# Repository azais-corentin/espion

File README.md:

# espion

Multi-camera IR marker tracking. Each camera board triggers its global-shutter sensor at
the same instant as every other board, finds the IR blobs at 120 fps, computes subpixel
centroids and streams them over Ethernet (UDP). The host triangulates 3D marker positions,
runs calibration and coordinates time sync.

**Status:** firmware and host apps are stubs that build. The camera board's schematic is
captured in KiCad (hierarchical, wired, ERC clean); PCB layout has not started.

## Hardware

A custom KiCad baseboard for a Waveshare ESP32-P4-Core module (ESP32-P4 rev v3, 32 MB
in-package PSRAM, 16 MB flash). The P4 does the vision: it captures an OV9281 (1 MP
monochrome global shutter, MIPI CSI-2, 640×400 binned at 120 fps) triggered on its XVS pin,
and runs blob detection. An 850 nm LED ring (12 × 90° LEDs, ≈ 0.9 A pulses) lights passive
retroreflective markers at room scale (2–5 m). It is gated by the sensor's STROBE output,
with a P4 enable line for dark frames. The P4's own Ethernet MAC with an IP101GRI PHY
(100 Mbit/s) sends UDP to the host and keeps the boards' clocks in sync with PTP (IEEE 1588,
hardware timestamps; target: about 1 µs). The boards elect the PTP grandmaster among
themselves, with automatic failover. The board is powered over PoE (802.3af) or USB-C at
5 V; USB-C also flashes and debugs the P4.

The board's schematic, PCB and 3D view are published at
<https://azais-corentin.github.io/espion/> (Ferrite's web viewer, rebuilt when the board
changes on `main`).

## Layout

| Path | Content |
|---|---|
| `crates/espion-proto/` | no_std UDP wire format shared by firmware and host; the camera stream (raw and JPEG frames, remote settings) is implemented |
| `firmware/cam-p4/` | ESP32-P4: camera, blob detection, XVS trigger, LED gating, Ethernet/UDP, PTP sync |
| `firmware/esp32p4-cache/` | no_std cache maintenance for the P4 behind one lock shared by both cores, and the cache prefetch set-up |
| `firmware/esp32p4-csi/` | no_std MIPI CSI-2 receiver driver for the P4 (esp-hal lacks one) |
| `firmware/esp32p4-jpeg/` | no_std hardware JPEG encoder driver for the P4, greyscale (esp-hal lacks one) |
| `firmware/esp32p4-perf/` | no_std performance counters of the P4: cycles, instructions, branches, mispredictions, stores, cache hits and misses; marker pins through the dedicated-IO CSRs |
| `firmware/esp32p4-pie/` | no_std PIE (128-bit vector) kernels for the P4 on stable Rust: instruction encoders and the dark-skip scan |
| `firmware/espion-core1/` | no_std runner of the blob detector on a bare second core of the P4, and core 0's handle that starts and watches it; optional marker pins for a logic analyser |
| `firmware/espion-vision/` | no_std blob detector: threshold, 8-connected components, intensity-weighted subpixel centroids, on RAW8 and RAW10 rows; tested on the host |
| `firmware/poc-p4-stream/` | Proof of concept on the Waveshare ESP32-P4-ETH: streams the OV9281 to the host over Ethernet (raw or JPEG) and takes its settings from there |
| `firmware/ov9281/` | no_std OV9281 sensor driver: computes a mode (format, size, crop/binning, frame rate) and drives the sensor over SCCB |
| `host/espion-server/` | UDP receive + triangulation (CLI) |
| `host/espion-viewer/` | egui live view |
| `host/espion-calib/` | Intrinsics + extrinsics calibration |
| `host/espion-sync/` | Time-sync coordinator |
| `host/poc-viewer/` | Live view and control of the `poc-p4-stream` camera, with a fake camera for working without the board |
| `hardware/` | KiCad project (`espion-cam/`) and local libraries with their 3D models (`lib/`) |
| `docs/` | [architecture](docs/architecture.md), [protocol](docs/protocol.md), [timing](docs/timing.md), [board design](docs/hardware/README.md) |

## Dev environment

Needs Nix with flakes. The dev shell provides Rust 1.99.1 with the host and
`riscv32imafc-unknown-none-elf` (P4) targets, espflash, probe-rs, KiCad 10 and SolidCraft
(builds the library parts' 3D models).

```sh
direnv allow        # or: nix develop
```

Local overrides (e.g. `ESPFLASH_PORT`) go in `.envrc.local`, which is git-ignored.

Entering the dev shell installs the git hooks (`hk.pkl`): commit messages must follow
[Conventional Commits](https://www.conventionalcommits.org/), with the scopes in
`cog.toml`. See the Commits section of `AGENTS.md`.

## Build, flash, run

Host workspace (repo root; includes `espion-proto`):

```sh
cargo build --workspace
cargo test --workspace
cargo run -p espion-server   # TODO: stub, does nothing yet
cargo run -p espion-viewer   # TODO: stub
cargo run -p espion-calib    # TODO: stub
cargo run -p espion-sync     # TODO: stub
cargo run -p poc-viewer --release             # the ESP32-P4-ETH camera on eth0
cargo run -p poc-viewer --release -- --fake   # the same against a fake camera, no board
```

Firmware (own target, runner and lockfile; run from its directory):

```sh
cd firmware/cam-p4 && cargo build --release   # also builds firmware/esp32p4-csi

# TODO: untested (no board yet). The P4's USB Serial/JTAG shows up on the board's USB-C
# port. Flashes and opens the monitor:
cd firmware/cam-p4 && ESPFLASH_PORT=/dev/ttyACM0 cargo run --release
```

Hardware:

```sh
kicad hardware/espion-cam/espion-cam.kicad_pro
kicad-cli sch erc hardware/espion-cam/espion-cam.kicad_sch

# Rebuild a library part's 3D model from its SolidCraft script:
solidcraft-cli run hardware/lib/3d-src/<Footprint>.json --out hardware/lib/<Library>.3dshapes/<Footprint>.step
```

Library conventions and KLC checks: [hardware/lib/README.md](hardware/lib/README.md).

## License

Code: [MIT](LICENSE-MIT) or [Apache-2.0](LICENSE-APACHE), at your option.
Hardware (`hardware/`): [CERN-OHL-P-2.0](hardware/LICENSE).

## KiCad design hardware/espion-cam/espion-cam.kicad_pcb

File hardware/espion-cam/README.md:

# espion-cam

KiCad project for the espion camera board: a baseboard for the Waveshare ESP32-P4-Core
module. The schematic is captured and ERC clean: a root sheet and seven hierarchical sheets
(power, mcu, ethernet, camera, led_driver, led_ring, imu), with the multi-signal interfaces
crossing sheets as buses. The board is fully placed and routed (4 layers, 64 × 64 mm,
JLCPCB Economic PCBA on the top side, hand-soldered parts listed in `.omp/kicad.json`).
Licensed under CERN-OHL-P-2.0 (`../LICENSE`).

## Board

- **MCU:** U6 Waveshare ESP32-P4-Core module (bottom side, hand-soldered, not on the stencil).
  Symbol `MCU_Module_Waveshare:ESP32-P4-Core`, footprint
  `Module_Waveshare:Waveshare_ESP32-P4-Core_HandSolder` (`../lib/`).
  [mcu](../../docs/hardware/mcu.md#module)
- **Camera:** off-board OV9281 global-shutter mono module behind a lens cutout, on a 15-pin 1.0 mm
  FFC (MIPI CSI-2, 2 lanes) through a notch in the board edge into J4 (AFA07 family, bottom
  contact). XVS (GPIO7) and STROBE come from the module's pads over a JST-SH 4-pin pigtail into J3:
  XVS through the R40/R44 divider, an assembly option; STROBE through U7 Tech Public TP74LV1T34 to the LED
  gate and GPIO12 (ETM capture). The CSI lanes run straight from J4 to U6, with no series-resistor positions.
  [camera](../../docs/hardware/camera.md)
- **LED:** 850 nm ring D4–D15, 12 × A-SC880IR3C in one string around the lens cutout. U10
  TPS61170 boost straight from +5V (`BST_EN`, GPIO53; PWM sets the
  output) into the storage capacitors C46/C47, U11 TLV9061 + Q1 HL2310A (SOT-23) current sink (R69
  sense) gated by `STROBE ∧ LED_EN` in U9 SN74LVC1G97 (`LED_EN`, GPIO11), with a hardware
  timeout per pulse behind the firmware exposure cap. No continuous-on mode. Firmware keeps
  +32V just above the string from a divider on Q1's drain (R70/R76, `LED_K_SENSE`, GPIO23), a
  required headroom loop: Q1 is not rated for full boost output.
  [led](../../docs/hardware/led.md)
- **Ethernet:** U1 IP101G PHY on RMII (Y1 crystal; the PHY supplies the REF_CLK), J1 LINK-PP
  LPJG0926HENL MagJack (bottom side, hand-soldered) with all four line-side centre taps brought out,
  its LEDs driven by the PHY, PPS and PHY reset test points. `PHY_RST_N` GPIO22.
  [ethernet](../../docs/hardware/ethernet.md)
- **Power:** U2 DP1435-5V IEEE 802.3af PoE PD module (isolated, bottom side, hand-soldered)
  straight to U4 TPS2121 priority mux (internal reference), OR-ed with USB-C 5 V (source
  on `PWR_SRC`, GPIO2); U3 TLV62569 buck to 3.3 V. [power](../../docs/hardware/power.md)
- **USB-C:** J2 straight to the P4's USB Serial/JTAG (no hub, GPIO24/25), U5 SRV05-4 ESD
  protection, D2 H7VHD3UA VBUS TVS. VBUS is not sensed: the D+ pull-up stays on.
  [mcu](../../docs/hardware/mcu.md#usb-c)
- **Status and buttons:** D1 YY-0807BRGK26 RGB status LED (`STATUS_LED`, GPIO13); SW1
  RESET and SW2 BOOT.
  [mcu](../../docs/hardware/mcu.md#status-led)
- **IMU:** U12 MSA3S02 3-axis accelerometer on its own I²C bus (GPIO3/4), INT1 on GPIO51: the
  motion interrupt flags a bumped camera, the accelerometer gives the gravity vector for rig
  calibration (no gyroscope). [imu](../../docs/hardware/imu.md)
- **Mechanical:** 4 × M3 plated mounting holes H1–H4, each pad on GND, kept clear of the PoE
  cable-side copper; 3 NPTH tooling holes TOOL1–TOOL3 (board-only) for JLCPCB Economic PCBA.
  [layout](../../docs/hardware/layout.md#board-and-stack-up)

Assembly: everything on the top side is machine-placed by JLCPCB Economic PCBA except the
hand-assembly list (`assembly.hand` in `.omp/kicad.json`; reasons in
[layout](../../docs/hardware/layout.md#assembly)).

Board design (decisions, requirements and their reasons, formulas, layout constraints,
firmware rules, the checks for the first boards): [`docs/hardware/`](../../docs/hardware/README.md).

The parts list is the schematic: every sourced symbol carries Manufacturer, MPN and LCSC fields,
and the project's BOM preset `Order` exports them. Read it with `kicad_query bom`, or generate
the CSV for each order (from this directory) and don't commit it:

```sh
kicad-cli sch export bom --preset Order -o espion-cam-bom.csv espion-cam.kicad_sch
```

The CSV has the columns Reference, Qty, Value, Footprint, Manufacturer, MPN, LCSC and DNP,
one row per group of identical parts, without DNP parts or parts excluded from the BOM.

Net classes (track widths, clearances, diff-pair geometry) are set in `espion-cam.kicad_pro`
for the JLCPCB JLC04161H-7628 stack-up (4 layers, 1.6 mm). The spacing rules that net
classes can't express (PoE isolation, MIPI CSI spacing and skew, MDI spacing, pair-to-pair spacing and skew, LED_PWR pad
spacing, the U12 LGA lands, hole spacing, power neck-downs and silkscreen) are in the custom
rules file `espion-cam.kicad_dru`; [layout](../../docs/hardware/layout.md#custom-rules) gives each one's reason.

System view: `../../docs/architecture.md`. Timing requirements for XVS, STROBE and PPS:
`../../docs/timing.md`.

## Conventions

- Edit only with KiCad (the dev shell provides KiCad 10). Never hand-edit `.kicad_*` files.
  Agents work through the KiCad toolkit instead (`kicad_query`, `kicad_edit`,
  `kicad_check`, `kicad_render`, `kicad_export`; see `../../AGENTS.md`).
- The schematic and the board are the source of every value. `docs/hardware/` holds
  requirements, decisions, formulas, accepted risks, layout constraints, firmware rules and
  first-board checks, never values the KiCad files hold or that are calculated from them. A
  change updates `../../docs/hardware/` in the same commit when it changes one of those. A
  part change also updates the symbol's Manufacturer, MPN and LCSC fields. A new or removed
  block or IC family updates the board list above. There is no committed BOM file.
- Keep ERC at 0 violations: `kicad-cli sch erc espion-cam.kicad_sch` (from this directory).
- Project-specific symbols, footprints and 3D models go in `../lib/` (conventions and KLC
  checks in `../lib/README.md`), not in global libraries.
- Fabrication outputs (Gerbers, drill files, BOM/CPL exports) and KiCad's `.history/` are
  not committed. Generate the outputs for each release (`kicad_export` writes them to
  `fab/`).

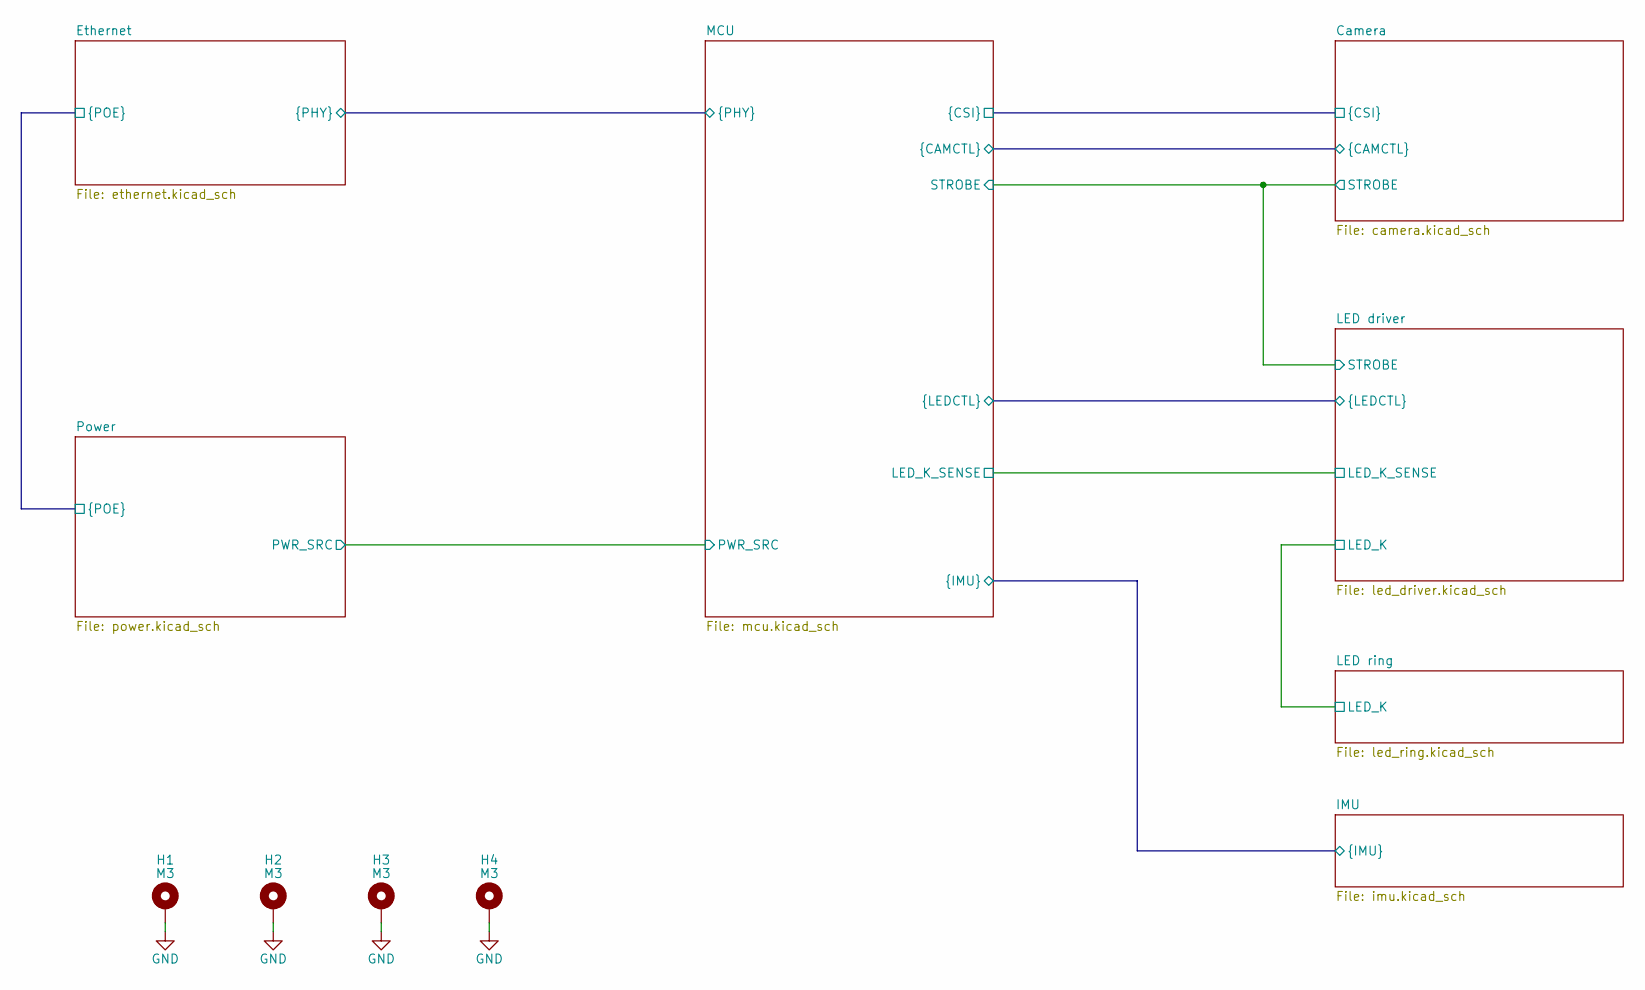
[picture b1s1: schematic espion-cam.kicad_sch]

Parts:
H1, H2, H3, H4: M3; MountingHole_3.2mm_M3_Pad

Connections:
GND: H1.1 (1_1), H2.1 (1_1), H3.1 (1_1), H4.1 (1_1); also elsewhere on the board

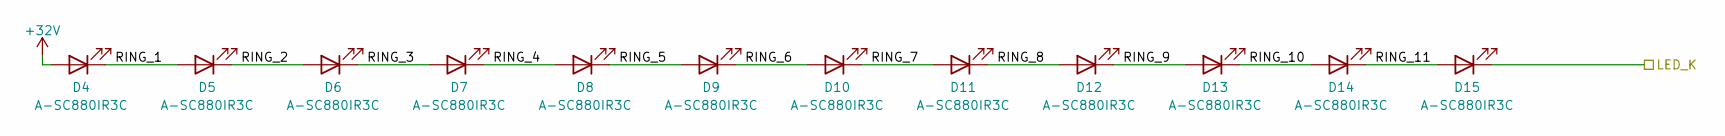
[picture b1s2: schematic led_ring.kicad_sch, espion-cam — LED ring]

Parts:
D4, D5, D6, D7, D8, D9, D10, D11, D12, D13, D14, D15: A-SC880IR3C; LED_Amicc_A-SC880IR3C_3.85x3.85mm; MPN A-SC880IR3C-P03-1T; LCSC C5355470

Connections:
+32V: D4.2 (A); also elsewhere on the board
/LED driver/LED_K: D15.1 (K); also elsewhere on the board
/LED ring/RING_1: D4.1 (K), D5.2 (A)
/LED ring/RING_2: D5.1 (K), D6.2 (A)
/LED ring/RING_3: D6.1 (K), D7.2 (A)
/LED ring/RING_4: D7.1 (K), D8.2 (A)
/LED ring/RING_5: D8.1 (K), D9.2 (A)
/LED ring/RING_6: D9.1 (K), D10.2 (A)
/LED ring/RING_7: D10.1 (K), D11.2 (A)
/LED ring/RING_8: D11.1 (K), D12.2 (A)
/LED ring/RING_9: D12.1 (K), D13.2 (A)
/LED ring/RING_10: D13.1 (K), D14.2 (A)
/LED ring/RING_11: D14.1 (K), D15.2 (A)

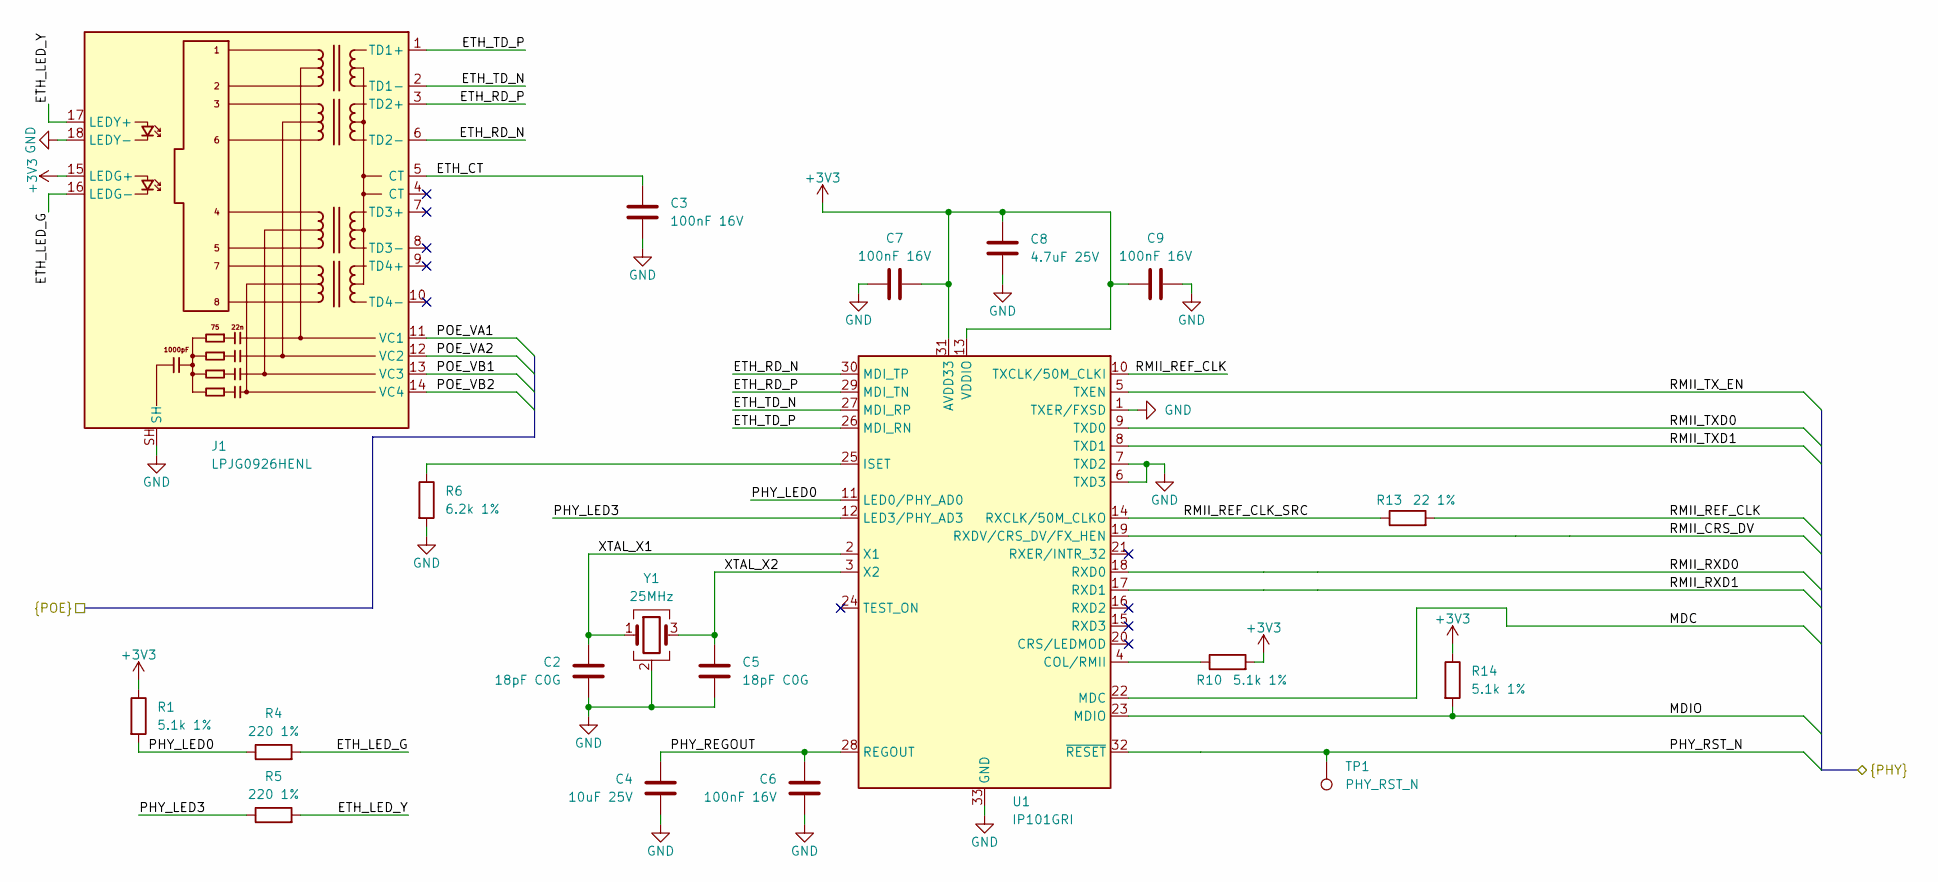
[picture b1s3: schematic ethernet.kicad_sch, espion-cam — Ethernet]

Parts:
C2, C5: 18pF C0G; C_0402_1005Metric; MPN 0402CG180J500NT; LCSC C1549
C3, C6, C7, C9: 100nF 16V; C_0402_1005Metric; MPN CL05B104KO5NNNC; LCSC C1525
C4: 10uF 25V; C_0805_2012Metric; MPN CL21A106KAYNNNE; LCSC C15850
C8: 4.7uF 25V; C_0805_2012Metric; MPN CL21A475KAQNNNE; LCSC C1779
J1: LPJG0926HENL; RJ45_LinkPP_LPJG0926HENL_Horizontal; MPN LPJG0926HENL; LCSC C22457393
R1, R10, R14: 5.1k 1%; R_0402_1005Metric; MPN 0402WGF5101TCE; LCSC C25905
R4, R5: 220 1%; R_0402_1005Metric; MPN 0402WGF2200TCE; LCSC C25091
R6: 6.2k 1%; R_0603_1608Metric; MPN 0603WAF6201T5E; LCSC C4260
R13: 22 1%; R_0402_1005Metric; MPN 0402WGF220JTCE; LCSC C25092
TP1: PHY_RST_N; TestPoint_Pad_D1.0mm
U1: IP101GRI; QFN-32-1EP_4x4mm_P0.4mm_EP2.65x2.65mm; MPN IP101GRI; LCSC C703537
Y1: 25MHz; Crystal_SMD_3225-4Pin_3.2x2.5mm; MPN X1E0000210139; LCSC C91750

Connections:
+3V3: C7.1, C8.1, C9.1, J1.15 (LEDG+), R1.1, R10.2, R14.1, U1.13 (VDDIO), U1.31 (AVDD33); also elsewhere on the board
/Ethernet/ETH_CT: C3.1, J1.5 (CT)
/Ethernet/ETH_LED_G: J1.16 (LEDG-), R4.2
/Ethernet/ETH_LED_Y: J1.17 (LEDY+), R5.2
/Ethernet/ETH_RD_N: J1.6 (TD2-), U1.30 (MDI_TP)
/Ethernet/ETH_RD_P: J1.3 (TD2+), U1.29 (MDI_TN)
/Ethernet/ETH_TD_N: J1.2 (TD1-), U1.27 (MDI_RP)
/Ethernet/ETH_TD_P: J1.1 (TD1+), U1.26 (MDI_RN)
/Ethernet/MDC: U1.22 (MDC); also elsewhere on the board
/Ethernet/MDIO: R14.2, U1.23 (MDIO); also elsewhere on the board
/Ethernet/PHY_LED0: R1.2, R4.1, U1.11 (LED0/PHY_AD0)
/Ethernet/PHY_LED3: R5.1, U1.12 (LED3/PHY_AD3)
/Ethernet/PHY_REGOUT: C4.1, C6.1, U1.28 (REGOUT)
/Ethernet/PHY_RST_N: TP1.1 (1_1), U1.32 (~RESET); also elsewhere on the board
/Ethernet/POE_VA1: J1.11 (VC1); also elsewhere on the board
/Ethernet/POE_VA2: J1.12 (VC2); also elsewhere on the board
/Ethernet/POE_VB1: J1.13 (VC3); also elsewhere on the board
/Ethernet/POE_VB2: J1.14 (VC4); also elsewhere on the board
/Ethernet/RMII_CRS_DV: U1.19 (RXDV/CRS_DV/FX_HEN); also elsewhere on the board
/Ethernet/RMII_REF_CLK: R13.2, U1.10 (TXCLK/50M_CLKI); also elsewhere on the board
/Ethernet/RMII_REF_CLK_SRC: R13.1, U1.14 (RXCLK/50M_CLKO)
/Ethernet/RMII_RXD0: U1.18 (RXD0); also elsewhere on the board
/Ethernet/RMII_RXD1: U1.17 (RXD1); also elsewhere on the board
/Ethernet/RMII_TXD0: U1.9 (TXD0); also elsewhere on the board
/Ethernet/RMII_TXD1: U1.8 (TXD1); also elsewhere on the board
/Ethernet/RMII_TX_EN: U1.5 (TXEN); also elsewhere on the board
/Ethernet/XTAL_X1: C2.1, U1.2 (X1), Y1.1
/Ethernet/XTAL_X2: C5.1, U1.3 (X2), Y1.3
GND: C2.2, C3.2, C4.2, C5.2, C6.2, C7.2, C8.2, C9.2, J1.18 (LEDY-), J1.SH, R6.2, U1.1 (TXER/FXSD), U1.6 (TXD3), U1.7 (TXD2), U1.33 (GND), Y1.2 (G), Y1.4 (G); also elsewhere on the board
unnamed: R10.1, U1.4 (COL/RMII)
unnamed: R6.1, U1.25 (ISET)

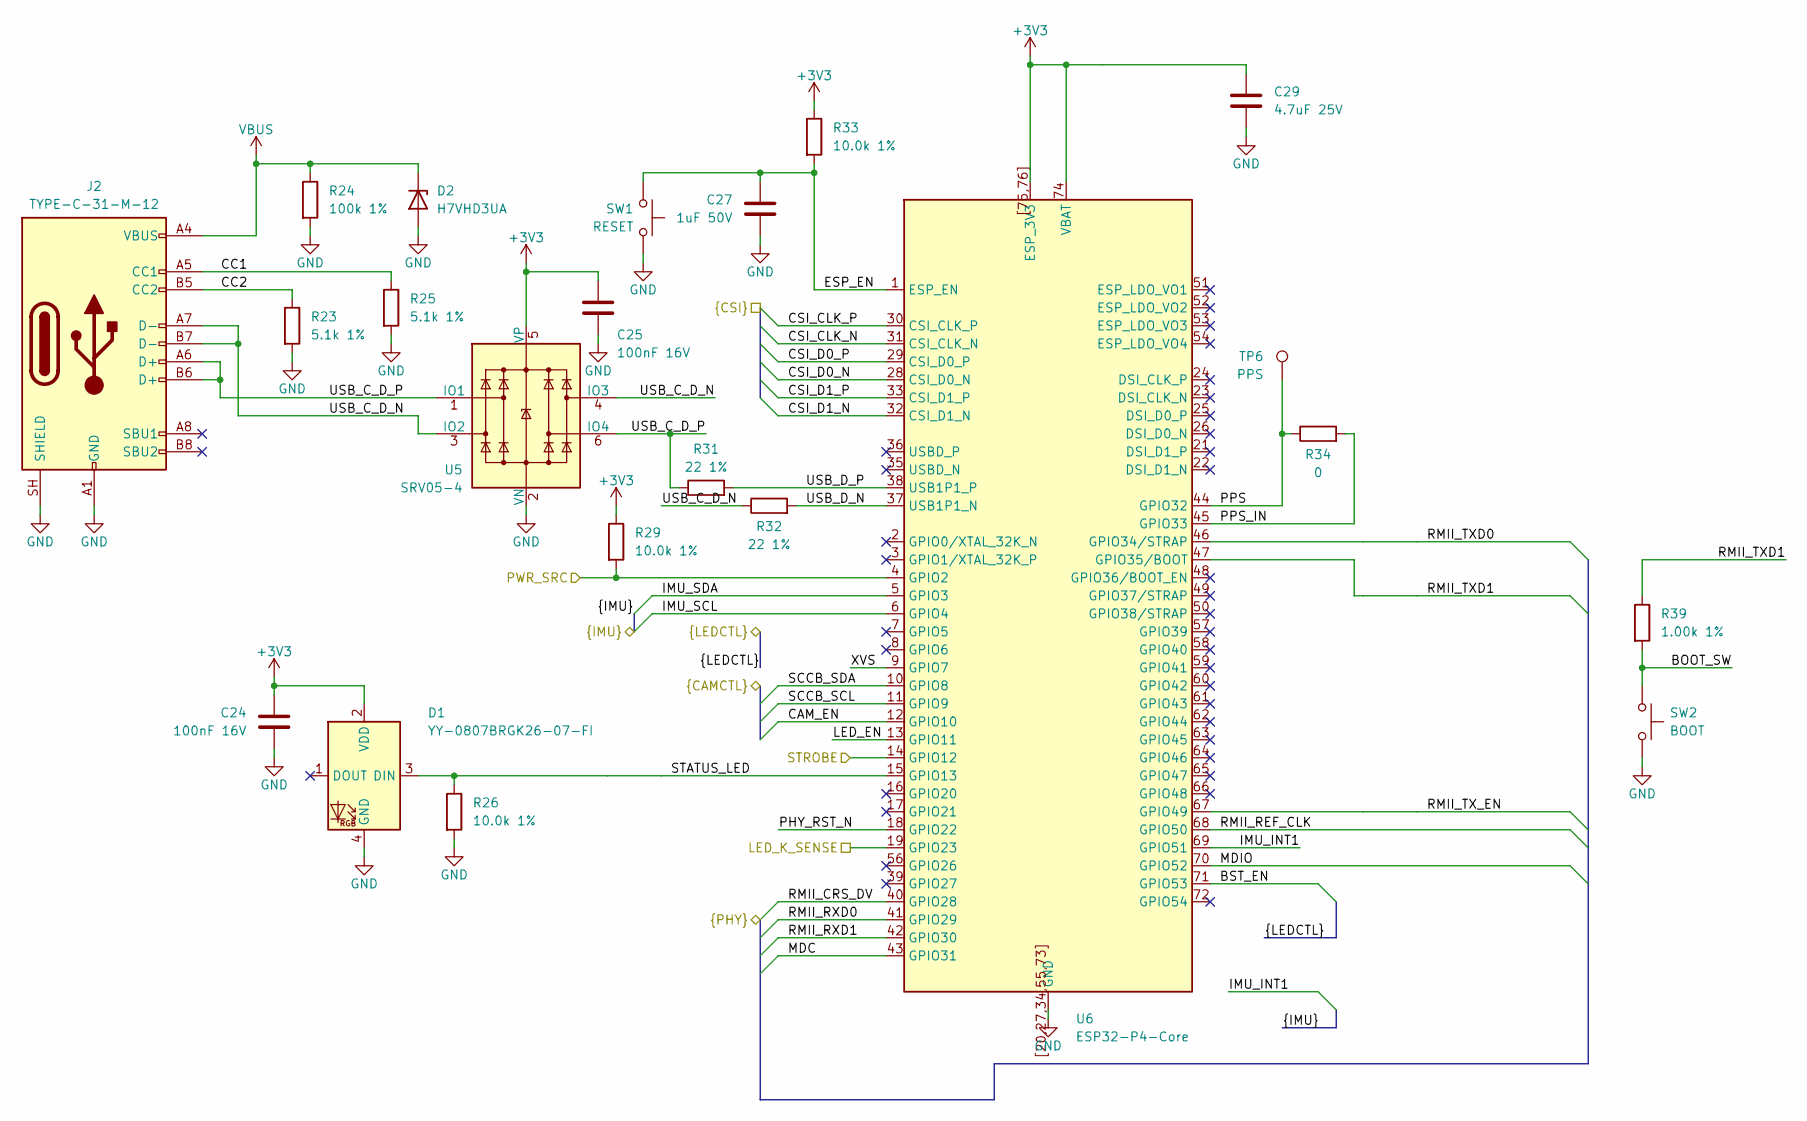
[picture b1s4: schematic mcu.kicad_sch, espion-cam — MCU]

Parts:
C24, C25: 100nF 16V; C_0402_1005Metric; MPN CL05B104KO5NNNC; LCSC C1525
C27: 1uF 50V; C_0805_2012Metric; MPN CL21B105KBFNNNE; LCSC C28323
C29: 4.7uF 25V; C_0805_2012Metric; MPN CL21A475KAQNNNE; LCSC C1779
D1: YY-0807BRGK26-07-FI; LED_Yongyu_YY-0807_2.0x1.7mm; MPN YY-0807BRGK26-07-FI; LCSC C54796802
D2: H7VHD3UA; D_SOD-323_HandSoldering; MPN H7VHD3UA; LCSC C20615807
J2: TYPE-C-31-M-12; USB_C_Receptacle_HRO_TYPE-C-31-M-12; MPN TYPE-C-31-M-12; LCSC C165948
R23, R25: 5.1k 1%; R_0402_1005Metric; MPN 0402WGF5101TCE; LCSC C25905
R24: 100k 1%; R_0402_1005Metric; MPN 0402WGF1003TCE; LCSC C25741
R26, R29, R33: 10.0k 1%; R_0402_1005Metric; MPN 0402WGF1002TCE; LCSC C25744
R31, R32: 22 1%; R_0402_1005Metric; MPN 0402WGF220JTCE; LCSC C25092
R34: 0; R_0402_1005Metric; MPN 0402WGF0000TCE; LCSC C17168
R39: 1.00k 1%; R_0402_1005Metric; MPN 0402WGF1001TCE; LCSC C11702
SW1: RESET; SW_Push_1P1T_XKB_TS-1187A; MPN TS-1187A-B-A-B; LCSC C318884
SW2: BOOT; SW_Push_1P1T_XKB_TS-1187A; MPN TS-1187A-B-A-B; LCSC C318884
TP6: PPS; TestPoint_Pad_D1.0mm
U5: SRV05-4; SOT-23-6; MPN SRV05-4; LCSC C7420376
U6: ESP32-P4-Core; Waveshare_ESP32-P4-Core_HandSolder; MPN ESP32-P4-Core (SKU 36096)

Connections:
+3V3: C24.1, C25.1, C29.1, D1.2 (VDD), R29.1, R33.1, U5.5 (VP), U6.74 (VBAT), U6.75 (ESP_3V3), U6.76 (ESP_3V3), U6.[75,76] (ESP_3V3); also elsewhere on the board
/Camera/CAM_EN: U6.12 (GPIO10); also elsewhere on the board
/Camera/CSI_CLK_N: U6.31 (CSI_CLK_N); also elsewhere on the board
/Camera/CSI_CLK_P: U6.30 (CSI_CLK_P); also elsewhere on the board
/Camera/CSI_D0_N: U6.28 (CSI_D0_N); also elsewhere on the board
/Camera/CSI_D0_P: U6.29 (CSI_D0_P); also elsewhere on the board
/Camera/CSI_D1_N: U6.32 (CSI_D1_N); also elsewhere on the board
/Camera/CSI_D1_P: U6.33 (CSI_D1_P); also elsewhere on the board
/Camera/SCCB_SCL: U6.11 (GPIO9); also elsewhere on the board
/Camera/SCCB_SDA: U6.10 (GPIO8); also elsewhere on the board
/Camera/STROBE: U6.14 (GPIO12); also elsewhere on the board
/Camera/XVS: U6.9 (GPIO7); also elsewhere on the board
/Ethernet/MDC: U6.43 (GPIO31); also elsewhere on the board
/Ethernet/MDIO: U6.70 (GPIO52); also elsewhere on the board
/Ethernet/PHY_RST_N: U6.18 (GPIO22); also elsewhere on the board
/Ethernet/RMII_CRS_DV: U6.40 (GPIO28); also elsewhere on the board
/Ethernet/RMII_REF_CLK: U6.68 (GPIO50); also elsewhere on the board
/Ethernet/RMII_RXD0: U6.41 (GPIO29); also elsewhere on the board
/Ethernet/RMII_RXD1: U6.42 (GPIO30); also elsewhere on the board
/Ethernet/RMII_TXD0: U6.46 (GPIO34/STRAP); also elsewhere on the board
/Ethernet/RMII_TXD1: R39.1, U6.47 (GPIO35/BOOT); also elsewhere on the board
/Ethernet/RMII_TX_EN: U6.67 (GPIO49); also elsewhere on the board
/LED driver/LED_K_SENSE: U6.19 (GPIO23); also elsewhere on the board
/MCU/BOOT_SW: R39.2, SW2.1
/MCU/BST_EN: U6.71 (GPIO53); also elsewhere on the board
/MCU/CC1: J2.A5 (CC1), R25.1
/MCU/CC2: J2.B5 (CC2), R23.1
/MCU/ESP_EN: C27.1, R33.2, SW1.1, U6.1 (ESP_EN)
/MCU/IMU_INT1: U6.69 (GPIO51); also elsewhere on the board
/MCU/IMU_SCL: U6.6 (GPIO4); also elsewhere on the board
/MCU/IMU_SDA: U6.5 (GPIO3); also elsewhere on the board
/MCU/LED_EN: U6.13 (GPIO11); also elsewhere on the board
/MCU/PPS: R34.1, TP6.1 (1_1), U6.44 (GPIO32)
/MCU/PPS_IN: R34.2, U6.45 (GPIO33)
/MCU/PWR_SRC: R29.2, U6.4 (GPIO2); also elsewhere on the board
/MCU/STATUS_LED: D1.3 (DIN), R26.1, U6.15 (GPIO13)
/MCU/USB_C_D_N: J2.A7 (D-), J2.B7 (D-), R32.1, U5.3 (IO2), U5.4 (IO3)
/MCU/USB_C_D_P: J2.A6 (D+), J2.B6 (D+), R31.1, U5.1 (IO1), U5.6 (IO4)
/MCU/USB_D_N: R32.2, U6.37 (USB1P1_N)
/MCU/USB_D_P: R31.2, U6.38 (USB1P1_P)
GND: C24.2, C25.2, C27.2, C29.2, D1.4 (GND), D2.2 (A), J2.A1 (GND), J2.A12 (GND), J2.B1 (GND), J2.B12 (GND), J2.SH (SHIELD), R23.2, R24.2, R25.2, R26.2, SW1.2, SW2.2, U5.2 (VN), U6.20 (GND), U6.27 (GND), U6.34 (GND), U6.55 (GND), U6.73 (GND), U6.[20,27,34,55,73] (GND); also elsewhere on the board
VBUS: D2.1 (K), J2.A4 (VBUS), J2.A9 (VBUS), J2.B4 (VBUS), J2.B9 (VBUS), R24.1; also elsewhere on the board

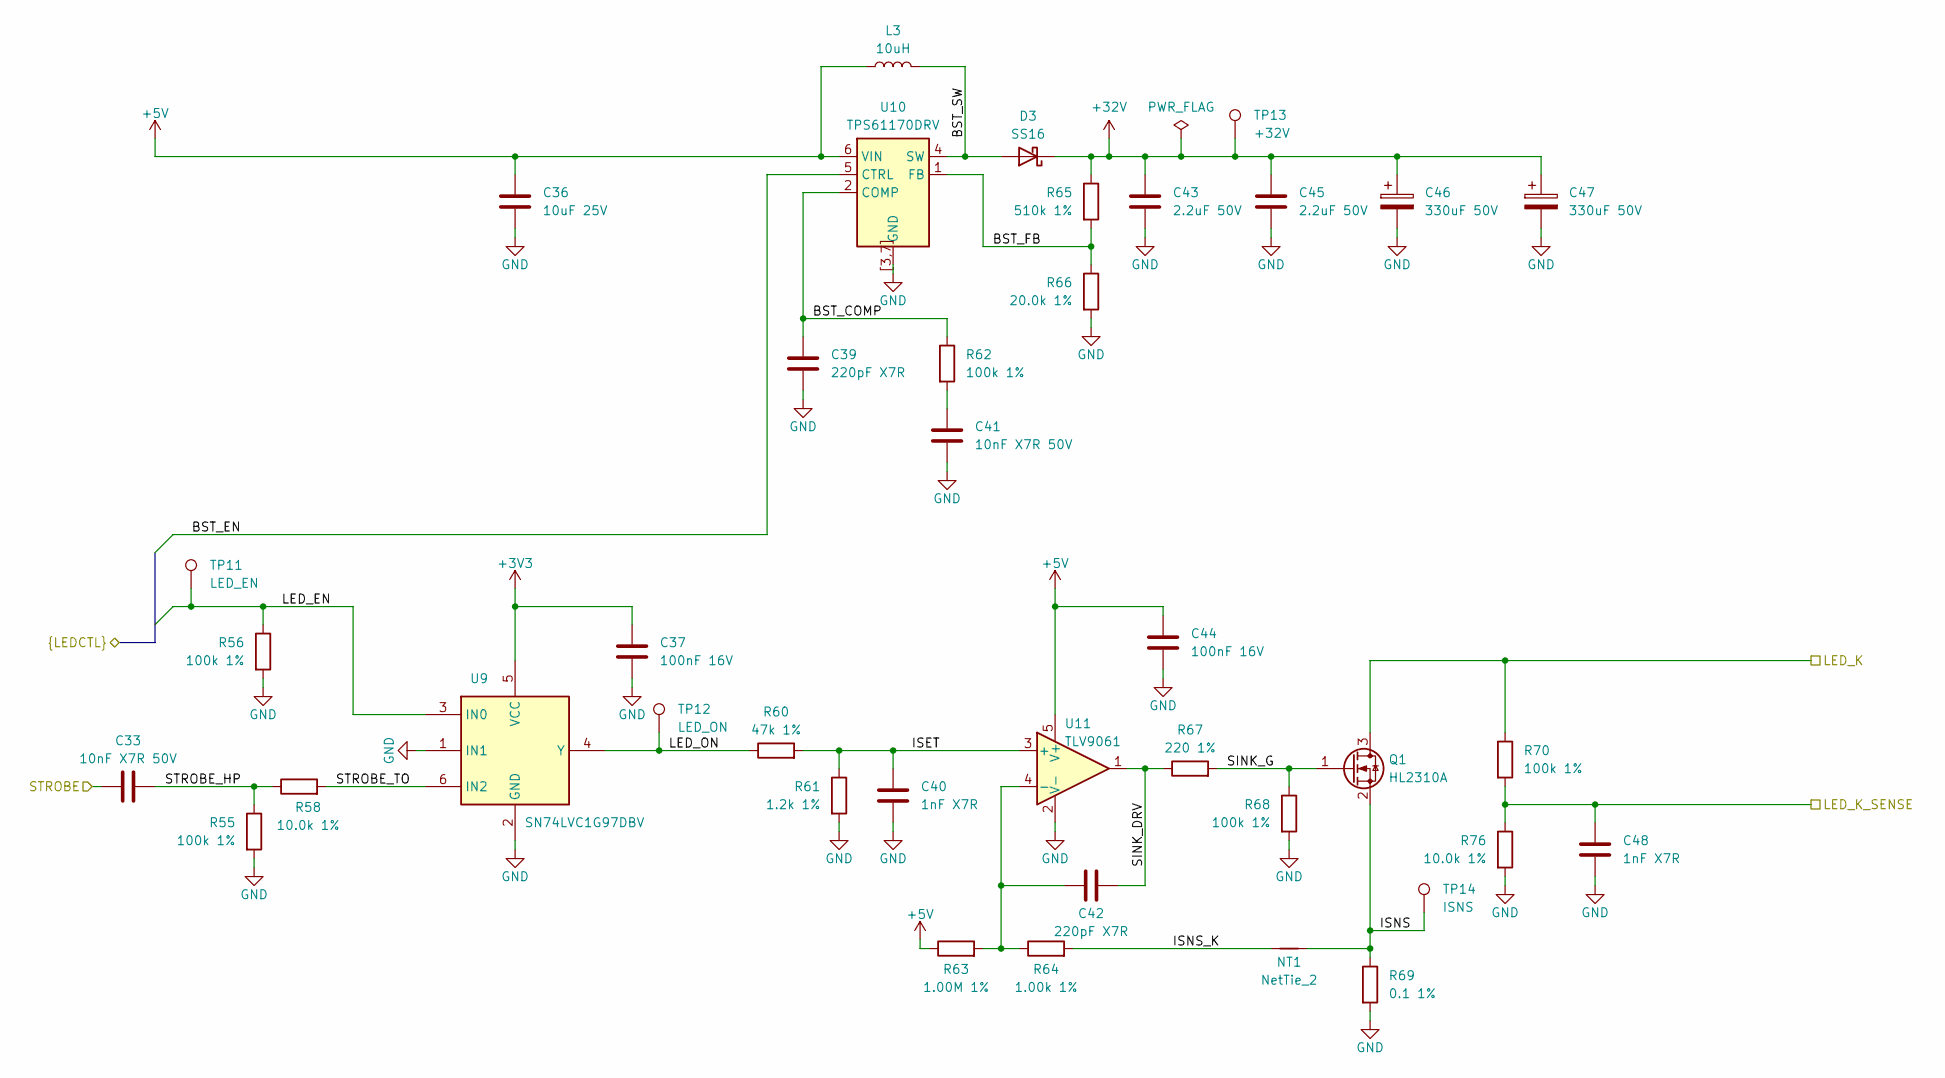
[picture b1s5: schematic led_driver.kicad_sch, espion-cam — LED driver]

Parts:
C33, C41: 10nF X7R 50V; C_0603_1608Metric; MPN 0603B103K500NT; LCSC C57112
C36: 10uF 25V; C_0805_2012Metric; MPN CL21A106KAYNNNE; LCSC C15850
C37, C44: 100nF 16V; C_0402_1005Metric; MPN CL05B104KO5NNNC; LCSC C1525
C39, C42: 220pF X7R; C_0402_1005Metric; MPN 0402B221K500NT; LCSC C1530
C40, C48: 1nF X7R; C_0402_1005Metric; MPN 0402B102K500NT; LCSC C1523
C43, C45: 2.2uF 50V; C_1206_3216Metric; MPN CL31B225KBHNNNE; LCSC C50254
C46, C47: 330uF 50V; CP_Elec_10x10; MPN GVZ1H337M1010CN; LCSC C22383763
D3: SS16; D_SMA; MPN SS16; LCSC C18199176
L3: 10uH; L_Changjiang_FNR4030S; MPN FNR4030S100MT; LCSC C167879
NT1: NetTie_2; NetTie-2_SMD_Pad0.5mm
Q1: HL2310A; SOT-23; MPN HL2310A; LCSC C7420347
R55, R56, R62, R68, R70: 100k 1%; R_0402_1005Metric; MPN 0402WGF1003TCE; LCSC C25741
R58, R76: 10.0k 1%; R_0402_1005Metric; MPN 0402WGF1002TCE; LCSC C25744
R60: 47k 1%; R_0402_1005Metric; MPN 0402WGF4702TCE; LCSC C25792
R61: 1.2k 1%; R_0402_1005Metric; MPN 0402WGF1201TCE; LCSC C25862
R63: 1.00M 1%; R_0402_1005Metric; MPN 0402WGF1004TCE; LCSC C26083
R64: 1.00k 1%; R_0402_1005Metric; MPN 0402WGF1001TCE; LCSC C11702
R65: 510k 1%; R_0603_1608Metric; MPN 0603WAF5103T5E; LCSC C23192
R66: 20.0k 1%; R_0402_1005Metric; MPN 0402WGF2002TCE; LCSC C25765
R67: 220 1%; R_0402_1005Metric; MPN 0402WGF2200TCE; LCSC C25091
R69: 0.1 1%; R_1206_3216Metric; MPN 1206W4F100LT5E; LCSC C25334
TP11: LED_EN; TestPoint_Pad_D1.0mm
TP12: LED_ON; TestPoint_Pad_D1.0mm
TP13: +32V; TestPoint_Pad_D1.5mm
TP14: ISNS; TestPoint_Pad_D1.0mm
U9: SN74LVC1G97DBV; SOT-23-6; MPN SN74LVC1G97DBVR; LCSC C128411
U10: TPS61170DRV; Texas_DRV0006A_WSON-6-1EP_2x2mm_P0.65mm_EP1x1.6mm; MPN TPS61170DRVR; LCSC C15163
U11: TLV9061; SOT-23-5; MPN TLV9061IDBVR; LCSC C398358

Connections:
+3V3: C37.1, U9.5 (VCC); also elsewhere on the board
+5V: C36.1, C44.1, L3.1, R63.1, U10.6 (VIN), U11.5 (V+); also elsewhere on the board
+32V: C43.1, C45.1, C46.1, C47.1, D3.1 (K), R65.1, TP13.1 (1_1); also elsewhere on the board
/Camera/STROBE: C33.1; also elsewhere on the board
/LED driver/BST_COMP: C39.1, R62.1, U10.2 (COMP)
/LED driver/BST_FB: R65.2, R66.1, U10.1 (FB)
/LED driver/BST_SW: D3.2 (A), L3.2, U10.4 (SW)
/LED driver/ISET: C40.1, R60.2, R61.1, U11.3 (+)
/LED driver/ISNS: NT1.1, Q1.2 (S), R69.1, TP14.1 (1_1)
/LED driver/ISNS_K: NT1.2, R64.2
/LED driver/LED_K: Q1.3 (D), R70.1; also elsewhere on the board
/LED driver/LED_K_SENSE: C48.1, R70.2, R76.1; also elsewhere on the board
/LED driver/LED_ON: R60.1, TP12.1 (1_1), U9.4 (Y)
/LED driver/SINK_DRV: C42.2, R67.1, U11.1
/LED driver/SINK_G: Q1.1 (G), R67.2, R68.1
/LED driver/STROBE_HP: C33.2, R55.1, R58.1
/LED driver/STROBE_TO: R58.2, U9.6 (IN2)
/MCU/BST_EN: U10.5 (CTRL); also elsewhere on the board
/MCU/LED_EN: R56.1, TP11.1 (1_1), U9.3 (IN0); also elsewhere on the board
GND: C36.2, C37.2, C39.2, C40.2, C41.2, C43.2, C44.2, C45.2, C46.2, C47.2, C48.2, R55.2, R56.2, R61.2, R66.2, R68.2, R69.2, R76.2, U9.1 (IN1), U9.2 (GND), U10.3 (GND), U10.7 (GND), U10.[3,7] (GND), U11.2 (V-); also elsewhere on the board
unnamed: C41.1, R62.2
unnamed: C42.1, R63.2, R64.1, U11.4 (-)

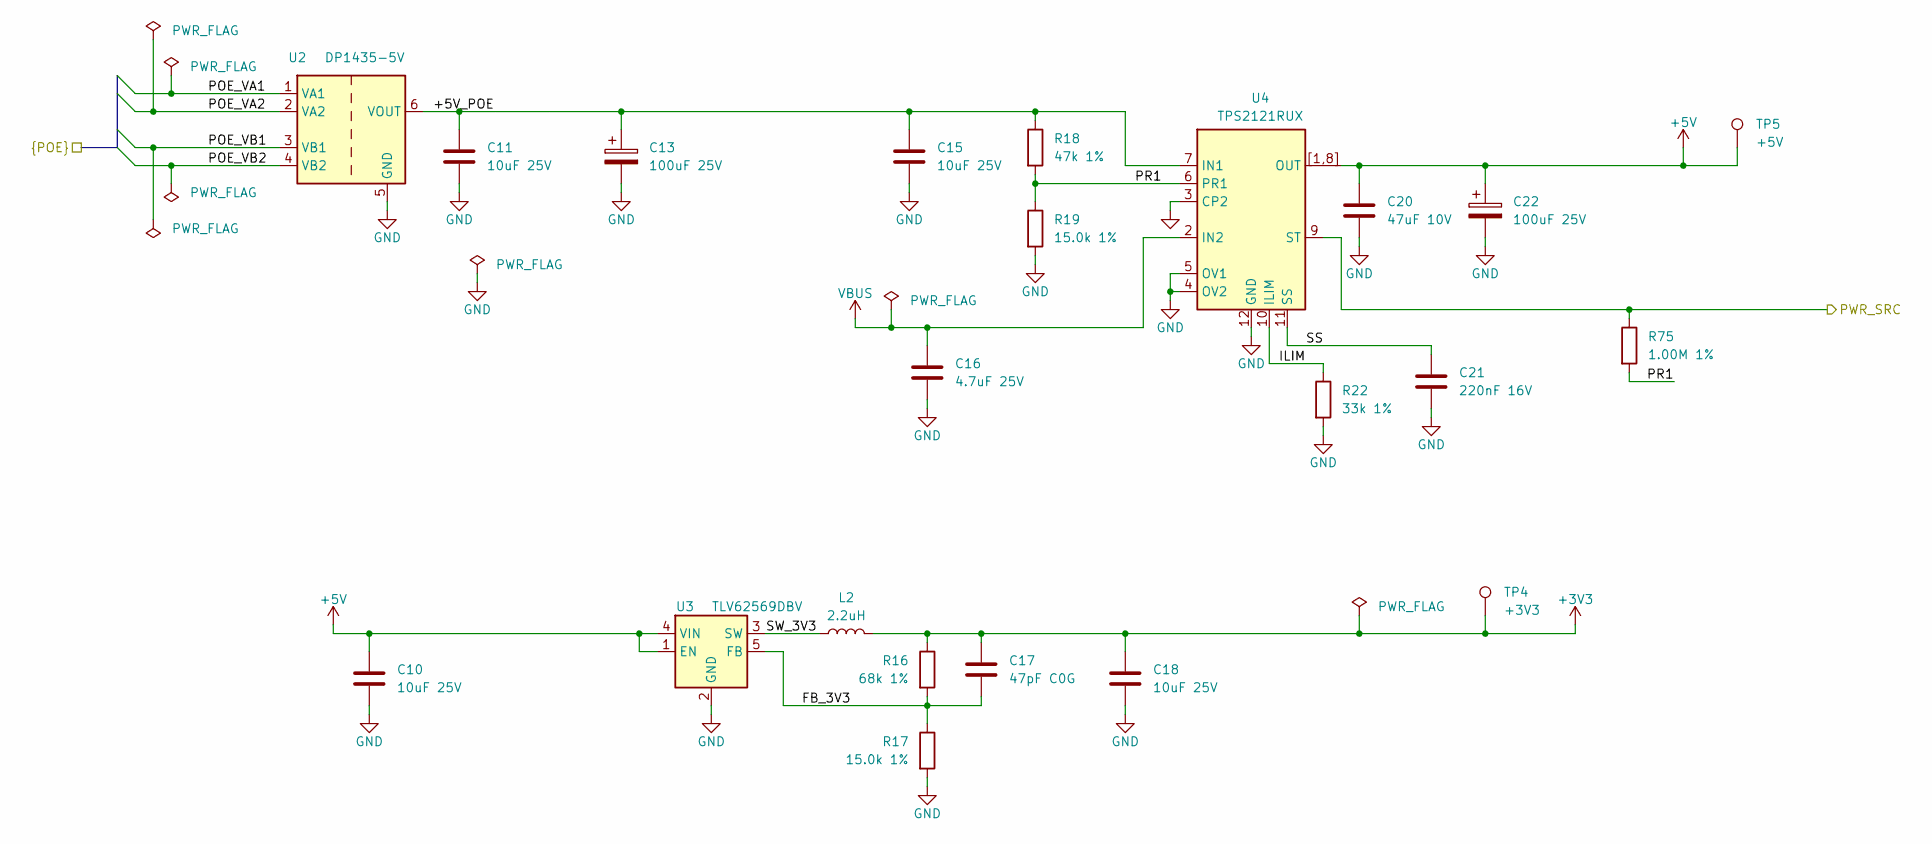
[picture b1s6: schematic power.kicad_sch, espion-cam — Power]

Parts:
C10, C11, C15, C18: 10uF 25V; C_0805_2012Metric; MPN CL21A106KAYNNNE; LCSC C15850
C13, C22: 100uF 25V; CP_Elec_6.3x5.8; MPN MA25V100M6x6; LCSC C46550465
C16: 4.7uF 25V; C_0805_2012Metric; MPN CL21A475KAQNNNE; LCSC C1779
C17: 47pF C0G; C_0402_1005Metric; MPN 0402CG470J500NT; LCSC C1567
C20: 47uF 10V; C_1206_3216Metric; MPN CL31A476MPHNNNE; LCSC C96123
C21: 220nF 16V; C_0402_1005Metric; MPN CL05B224KO5NNNC; LCSC C16772
L2: 2.2uH; L_Changjiang_FXL0630; MPN FXL0630-2R2-M; LCSC C167218
R16: 68k 1%; R_0402_1005Metric; MPN 0402WGF6802TCE; LCSC C36871
R17, R19: 15.0k 1%; R_0402_1005Metric; MPN 0402WGF1502TCE; LCSC C25756
R18: 47k 1%; R_0402_1005Metric; MPN 0402WGF4702TCE; LCSC C25792
R22: 33k 1%; R_0402_1005Metric; MPN 0402WGF3302TCE; LCSC C25779
R75: 1.00M 1%; R_0402_1005Metric; MPN 0402WGF1004TCE; LCSC C26083
TP4: +3V3; TestPoint_Pad_D1.5mm
TP5: +5V; TestPoint_Pad_D1.5mm
U2: DP1435-5V; Converter_DCDC_SDAPO_DP1435_THT; MPN DP1435-5V; LCSC C5380097
U3: TLV62569DBV; SOT-23-5; MPN TLV62569DBVR; LCSC C141836
U4: TPS2121RUX; Texas_RUX0012A_VQFN-HR-12_2x2.5mm_P0.5mm; MPN TPS2121RUXR; LCSC C485916

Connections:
+3V3: C17.1, C18.1, L2.2, R16.1, TP4.1 (1_1); also elsewhere on the board
+5V: C10.1, C20.1, C22.1, TP5.1 (1_1), U3.1 (EN), U3.4 (VIN), U4.1 (OUT), U4.8 (OUT), U4.[1,8] (OUT); also elsewhere on the board
/Ethernet/POE_VA1: U2.1 (VA1); also elsewhere on the board
/Ethernet/POE_VA2: U2.2 (VA2); also elsewhere on the board
/Ethernet/POE_VB1: U2.3 (VB1); also elsewhere on the board
/Ethernet/POE_VB2: U2.4 (VB2); also elsewhere on the board
/MCU/PWR_SRC: R75.1, U4.9 (ST); also elsewhere on the board
/Power/+5V_POE: C11.1, C13.1, C15.1, R18.1, U2.6 (VOUT), U4.7 (IN1)
/Power/FB_3V3: C17.2, R16.2, R17.1, U3.5 (FB)
/Power/ILIM: R22.1, U4.10 (ILIM)
/Power/PR1: R18.2, R19.1, R75.2, U4.6 (PR1)
/Power/SS: C21.1, U4.11 (SS)
/Power/SW_3V3: L2.1, U3.3 (SW)
GND: C10.2, C11.2, C13.2, C15.2, C16.2, C18.2, C20.2, C21.2, C22.2, R17.2, R19.2, R22.2, U2.5 (GND), U3.2 (GND), U4.3 (CP2), U4.4 (OV2), U4.5 (OV1), U4.12 (GND); also elsewhere on the board
VBUS: C16.1, U4.2 (IN2); also elsewhere on the board

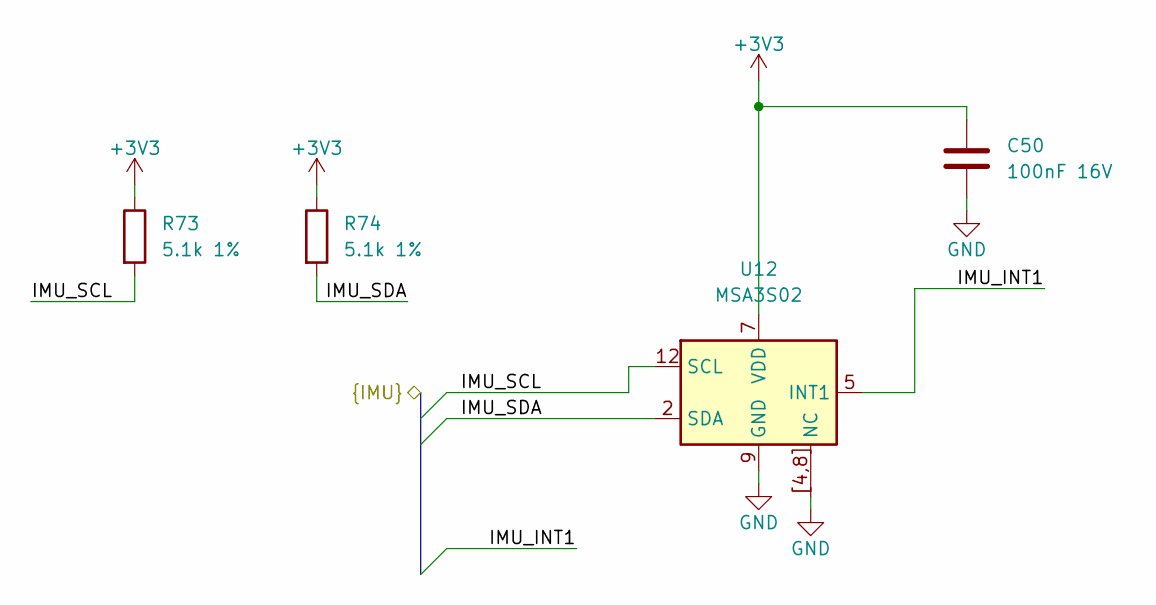
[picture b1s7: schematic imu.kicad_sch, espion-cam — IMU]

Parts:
C50: 100nF 16V; C_0402_1005Metric; MPN CL05B104KO5NNNC; LCSC C1525
R73, R74: 5.1k 1%; R_0402_1005Metric; MPN 0402WGF5101TCE; LCSC C25905
U12: MSA3S02; MEMSensing_LGA-12_2x2mm_P0.5mm_LayoutBorder2x4y; MPN MSA3S02; LCSC C51928204

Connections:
+3V3: C50.1, R73.1, R74.1, U12.7 (VDD); also elsewhere on the board
/MCU/IMU_INT1: U12.5 (INT1); also elsewhere on the board
/MCU/IMU_SCL: R73.2, U12.12 (SCL); also elsewhere on the board
/MCU/IMU_SDA: R74.2, U12.2 (SDA); also elsewhere on the board
GND: C50.2, U12.4 (NC), U12.8 (NC), U12.9 (GND), U12.[4,8] (NC); also elsewhere on the board
